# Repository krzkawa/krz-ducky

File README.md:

# krzducky

RP2040 hardware injection device.

## Repository Layout

* `pcb/` — KiCad schematic and board layout files also gerber files.
* `BOM.md` — Component parts list and AliExpress links.
* `firmware/` — CircuitPython and pico-ducky files.

## Hardware Specs

* **MCU:** RP2040 (QFN-56)
* **Flash:** 16MB W25Q128 (SOIC-8)
* **Power:** AP2112K-3.3 LDO (5V USB to 3.3V)
* **Passives:** 0603 size for hand-soldering / hot air assembly
* **Clock:** 12MHz 3225 crystal with 18pF load capacitors
* **Control:** Manual BOOTSEL tactile switch

## Flashing & Setup

1. Hold the **BOOTSEL** button and plug the device into a PC.
2. Drag `firmware/adafruit-circuitpython-*.uf2` onto the mounted `RPI-RP2` drive.
3. Once it reboots as `CIRCUITPY`, copy all files from `firmware/pico-ducky/` to the root of the `CIRCUITPY` drive.
4. Edit or create `payload.dd` on the drive with your DuckyScript commands.

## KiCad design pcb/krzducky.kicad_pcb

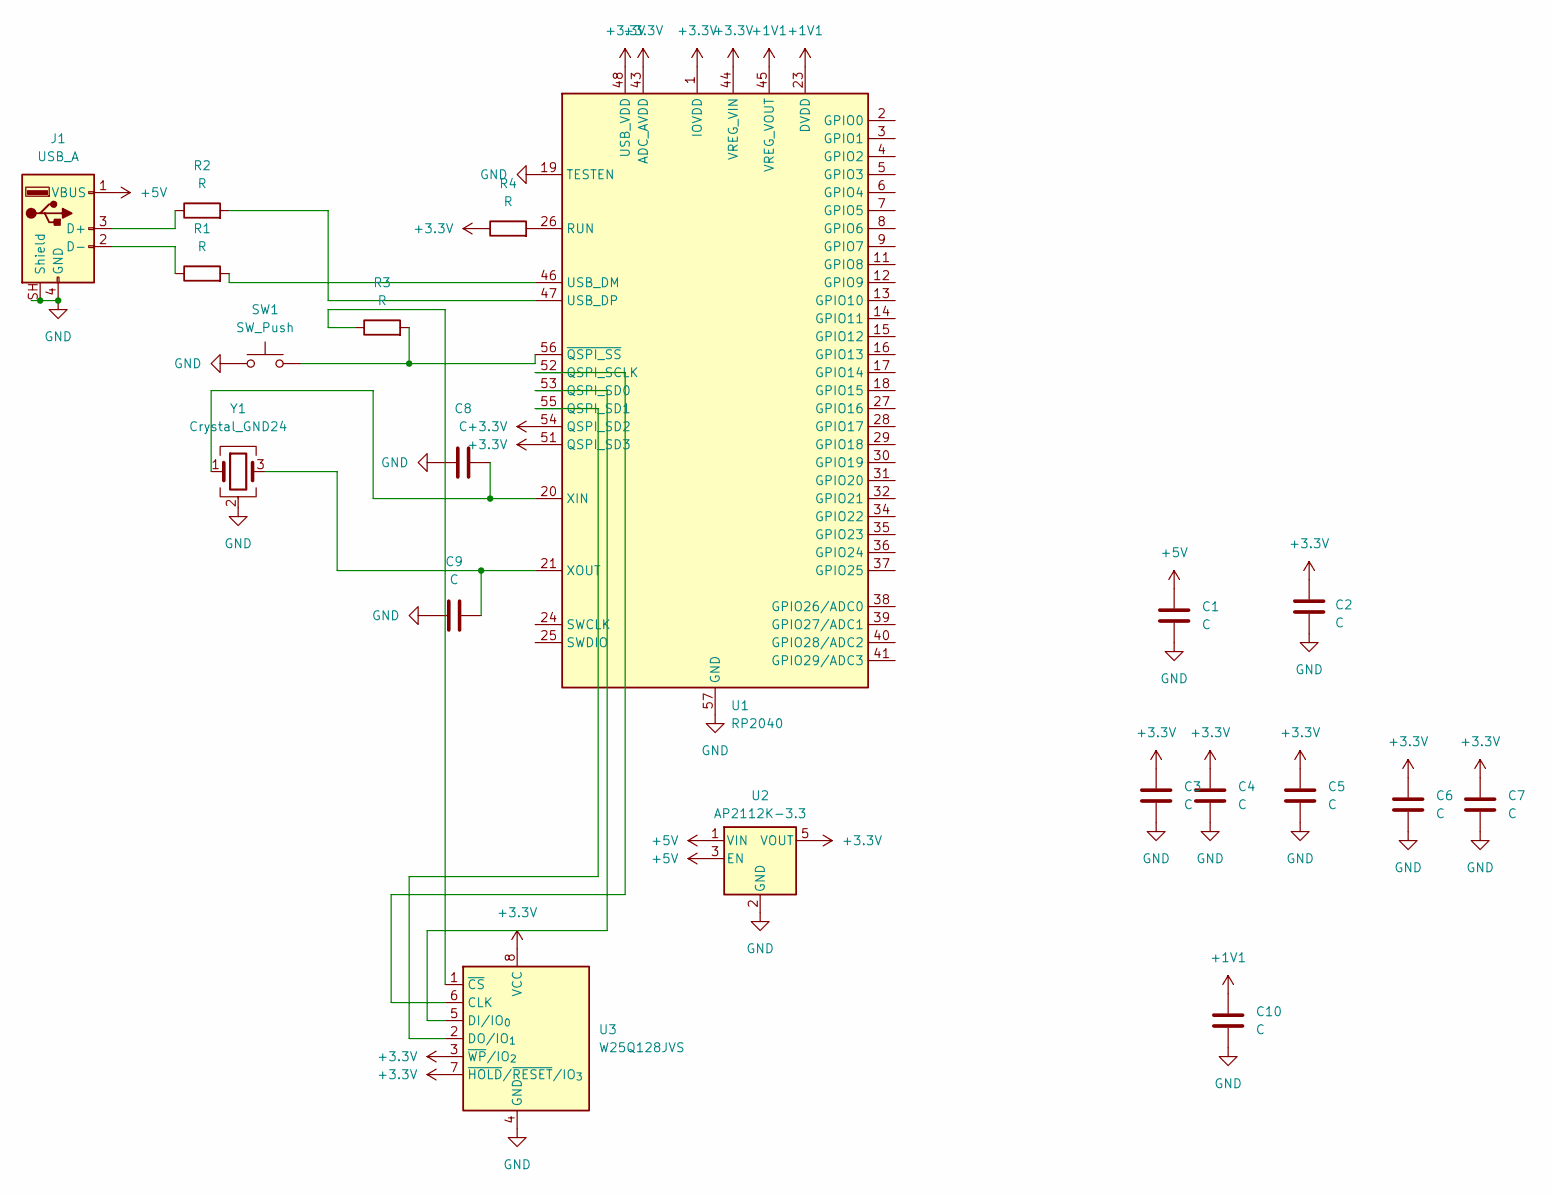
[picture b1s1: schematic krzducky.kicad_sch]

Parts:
C1, C2, C3, C4, C5, C6, C7, C8, C9, C10: C; C_0603_1608Metric_Pad1.08x0.95mm_HandSolder
J1: USB_A; USB_A_Molex_48037-2200_Horizontal
R1, R2, R3, R4: R; R_0603_1608Metric_Pad0.98x0.95mm_HandSolder
SW1: SW_Push; SW_SPST_PTS645Sx43SMTR92
U1: RP2040; QFN-56-1EP_7x7mm_P0.4mm_EP3.2x3.2mm
U2: AP2112K-3.3; SOT-23-5_HandSoldering
U3: W25Q128JVS; SOIC-8_3.9x4.9mm_P1.27mm
Y1: Crystal_GND24; Crystal_SMD_3225-4Pin_3.2x2.5mm_HandSoldering

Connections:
+1V1: C10.1, U1.23 (DVDD), U1.45 (VREG_VOUT), U1.50 (DVDD)
+3.3V: C2.1, C3.1, C4.1, C5.1, C6.1, C7.1, R4.1, U1.1 (IOVDD), U1.10 (IOVDD), U1.22 (IOVDD), U1.33 (IOVDD), U1.42 (IOVDD), U1.43 (ADC_AVDD), U1.44 (VREG_VIN), U1.48 (USB_VDD), U1.49 (IOVDD), U1.51 (QSPI_SD3), U1.54 (QSPI_SD2), U2.5 (VOUT), U3.3 (~WP/IO_{2}), U3.7 (~HOLD/~RESET/IO_{3}), U3.8 (VCC)
+5V: C1.1, J1.1 (VBUS), U2.1 (VIN), U2.3 (EN)
GND: C1.2, C2.2, C3.2, C4.2, C5.2, C6.2, C7.2, C8.1, C9.1, C10.2, J1.4 (GND), J1.SH (Shield), SW1.1, U1.19 (TESTEN), U1.57 (GND), U2.2 (GND), U3.4 (GND), Y1.2 (G), Y1.4 (G)
unnamed: J1.3 (D+), R2.1
unnamed: J1.2 (D-), R1.1
unnamed: U1.52 (QSPI_SCLK), U3.6 (CLK)
unnamed: U1.53 (QSPI_SD0), U3.5 (DI/IO_{0})
unnamed: U1.55 (QSPI_SD1), U3.2 (DO/IO_{1})
unnamed: R4.2, U1.26 (RUN)
unnamed: R1.2, U1.46 (USB_DM)
unnamed: R2.2, U1.47 (USB_DP)
unnamed: C8.2, U1.20 (XIN), Y1.1
unnamed: C9.2, U1.21 (XOUT), Y1.3
unnamed: R3.2, SW1.2, U1.56 (~QSPI_SS)
unnamed: R3.1, U3.1 (~CS)

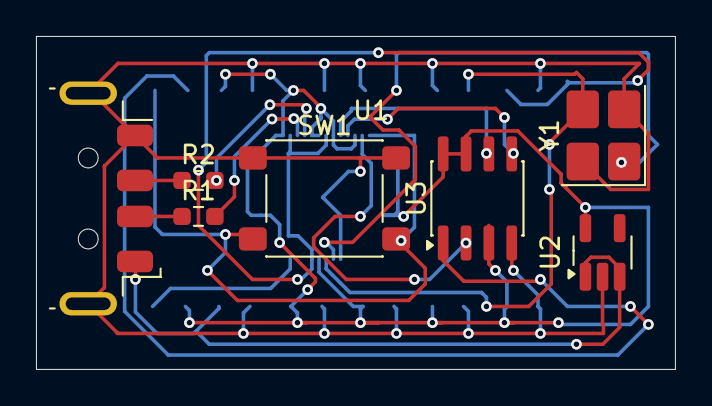
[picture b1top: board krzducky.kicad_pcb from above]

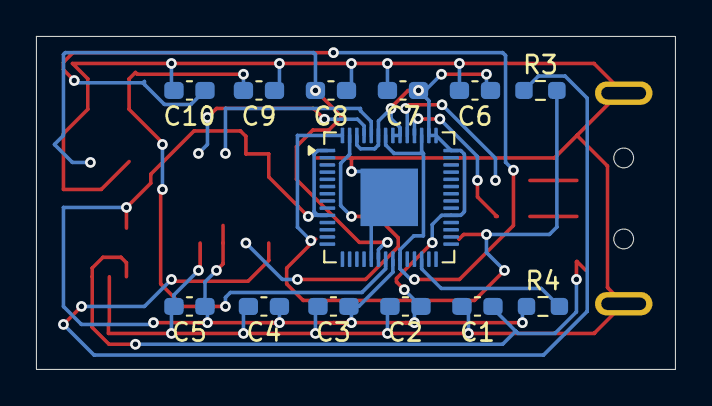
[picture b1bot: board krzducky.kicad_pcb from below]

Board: 2 copper layers, 35.5 x 18.5 mm, 20 parts (13 on the bottom side), 16 nets.

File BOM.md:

# Bill of Materials (BOM) — RP2040 Rubber Ducky

---

### Integrated Circuits & Core Components

| RefDes | Qty | Component / Description | Package | AliExpress Search Link |
|---|---|---|---|---|
| **U1** | 1 | RP2040 Microcontroller | QFN-56 (7x7mm) | [Search RP2040 QFN-56](https://www.aliexpress.com/w/wholesale-RP2040-QFN%25252d56.html) |
| **U2** | 1 | AP2112K-3.3 Voltage Regulator (3.3V 600mA LDO) | SOT-23-5 | [Search AP2112K-3.3 SOT-23-5](https://www.aliexpress.com/w/wholesale-AP2112K%25252d3.3-SOT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 |
| **U3** | 1 | W25Q128JVSIC Flash Memory (16MB NOR Flash) | SOIC-8 (208mil) | [Search W25Q128JVSIC SOIC-8](https://www.aliexpress.com/w/wholesale-W25Q128JVSIC-SOIC8.html) |
| **Y1** | 1 | 12MHz SMD Crystal (12pF, 4-pin) | 3225 (3.2x2.5mm) | [Search 12MHz SMD Crystal 3225](https://www.aliexpress.com/w/wholesale-12MHz-SMD-Crystal-3225.html) |
| **SW1** | 1 | Tactile Push Button (BOOTSEL) | 3x4mm / 2-pin SMD | [Search 3x4mm SMD Tactile Switch](https://www.aliexpress.com/w/wholesale-3x4mm-SMD-Tactile-Swi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 |
| **J1** | 1 | USB-A Male Plug Connector | Male PCB SMD Edge | [Search USB A Male SMD Connector](https://www.aliexpress.com/w/wholesale-USB-A-Male-SMD-Connec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 |

---

### Resistors (0603 SMD)

| RefDes | Qty | Value | Tolerance | Package | AliExpress Search Link |
|---|---|---|---|---|---|
| **R1, R2** | 2 | 27 Ω | ±1% | 0603 | [Search 27 Ohm 0603 Resistor](https://www.aliexpress.com/w/wholesale-27-Ohm-0603-Resistor.html) |
| **R3** | 1 | 1 kΩ | ±1% | 0603 | [Search 1k Ohm 0603 Resistor](https://www.aliexpress.com/w/wholesale-1k-Ohm-0603-Resistor.html) |
| **R4** | 1 | 10 kΩ | ±1% | 0603 | [Search 10k Ohm 0603 Resistor](https://www.aliexpress.com/w/wholesale-10k-Ohm-0603-Resistor.html) |

---

### Capacitors (0603 SMD)

| RefDes | Qty | Value | Voltage | Package | AliExpress Search Link |
|---|---|---|---|---|---|
| **C1, C2** | 2 | 10 µF | 16V (X5R/X7R) | 0603 | [Search 10uF 0603 Capacitor](https://www.aliexpress.com/w/wholesale-10uF-0603-Capacitor.html) |
| **C3–C7** | 5 | 100 nF | 16V (X7R) | 0603 | [Search 100nF 0603 Capacitor](https://www.aliexpress.com/w/wholesale-100nF-0603-Capacitor.html) |
| **C8, C9** | 2 | 18 pF | 50V (C0G/NP0) | 0603 | [Search 18pF 0603 Capacitor](https://www.aliexpress.com/w/wholesale-18pF-0603-Capacitor.html) |
| **C10** | 1 | 1 µF | 16V (X7R) | 0603 | [Search 1uF 0603 Capacitor](https://www.aliexpress.com/w/wholesale-1uF-0603-Capacitor.html) |
